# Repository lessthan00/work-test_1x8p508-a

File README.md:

# work-test-a

一种工作时测试用的工具  
将conn_p5.08_1x08转 conn_P5.08_1x08  
将conn_p5.08_1x08转 conn_P5.08_1x08带LED灯  
将conn_p5.08_1x04转 conn_P5.08_1x04

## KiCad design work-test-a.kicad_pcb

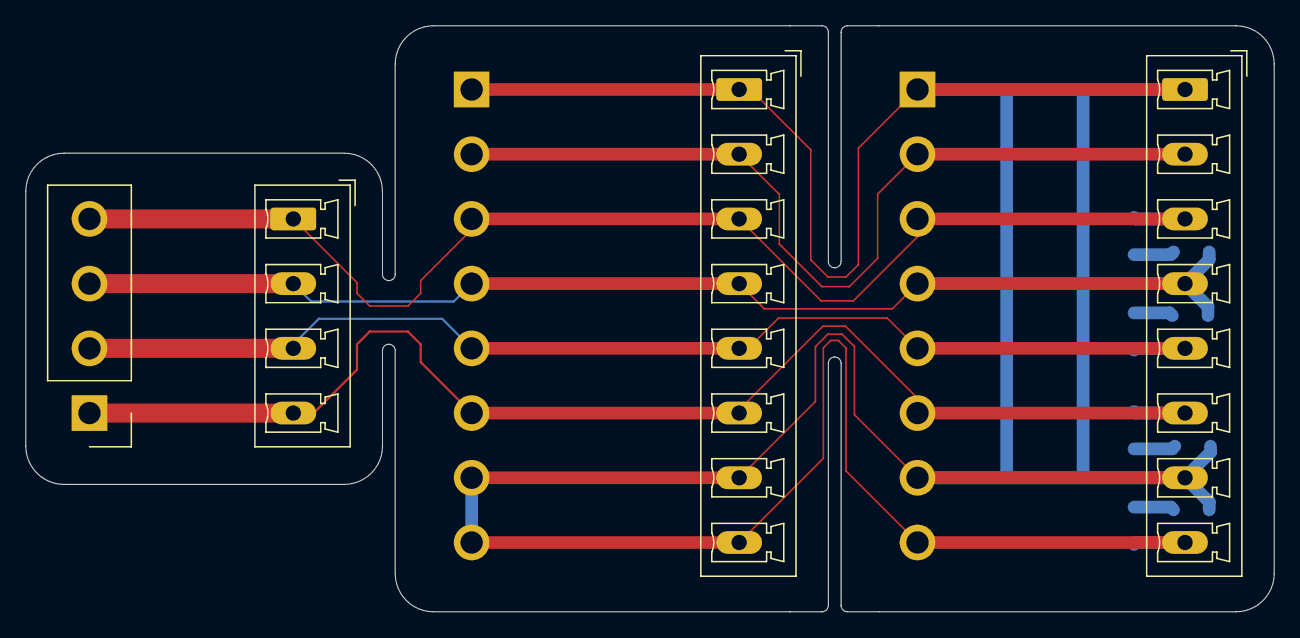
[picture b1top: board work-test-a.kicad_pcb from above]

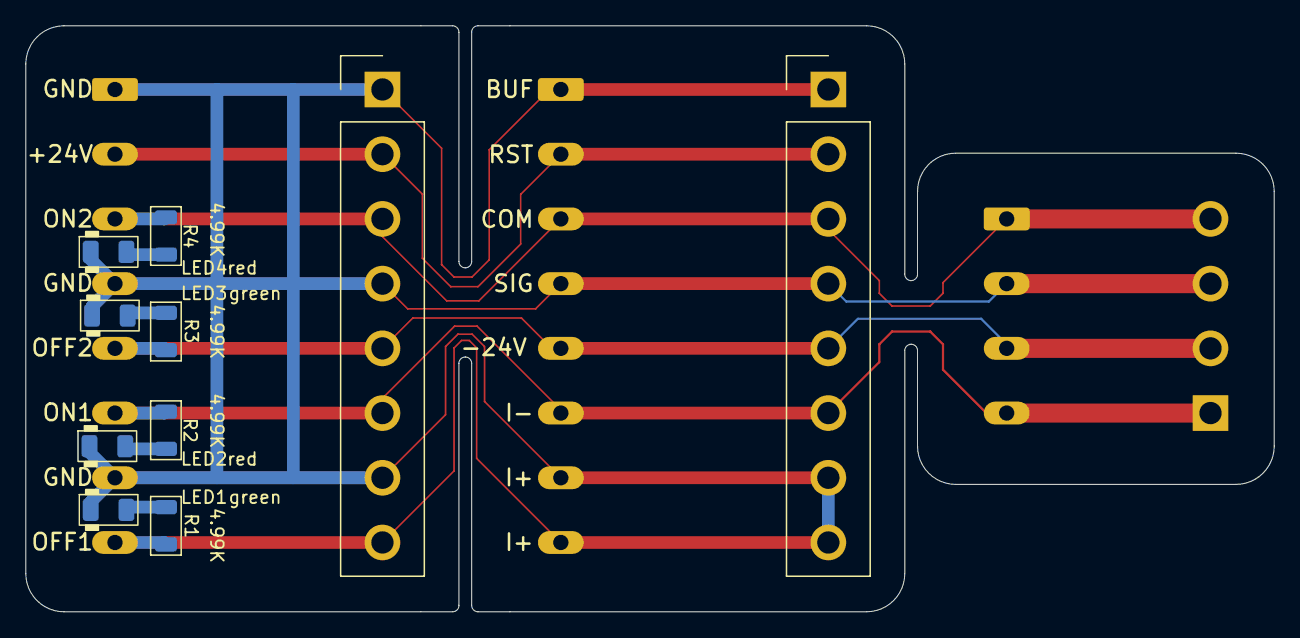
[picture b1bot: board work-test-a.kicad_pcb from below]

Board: 2 copper layers, 98.0 x 46.0 mm, 14 parts (10 on the bottom side), 17 nets.

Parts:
J1, J3: Conn_01x08; Samtec_HPM-08-01-x-S_Straight_1x08_Pitch5.08mm
J2, J4: JST_08; PhoenixContact_MCV_1,5_8-G-5.08_1x08_P5.08mm_Vertical
J5: JST_04; PhoenixContact_MCV_1,5_4-G-5.08_1x04_P5.08mm_Vertical
J6: Conn_01x04; Samtec_HPM-04-01-x-S_Straight_1x04_Pitch5.08mm
LED1, LED3: green; LED_1206_3216Metric
LED2, LED4: red; LED_1206_3216Metric
R1, R2, R3, R4: 4.99K; R_1206_3216Metric

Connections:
/+24V: J3.2, J4.2
/-24V: J1.5, J2.5, J5.3, J6.2
/BUF: J1.1, J2.1
/COM: J1.3, J2.3, J5.1, J6.4
/GND: J3.1, J3.4, J3.7, J4.1, J4.4, J4.7, LED1.1 (K), LED2.1 (K), LED3.1 (K), LED4.1 (K)
/Isig+: J1.7, J1.8, J2.7, J2.8
/Isig-: J1.6, J2.6, J5.4, J6.1
/RESET: J1.2, J2.2
/SIG: J1.4, J2.4, J5.2, J6.3
/close1: J3.8, J4.8, R1.1
/close2: J3.5, J4.5, R3.1
/open1: J3.6, J4.6, R2.1
/open2: J3.3, J4.3, R4.1
unnamed: LED1.2 (A), R1.2
unnamed: LED2.2 (A), R2.2
unnamed: LED3.2 (A), R3.2
unnamed: LED4.2 (A), R4.2
